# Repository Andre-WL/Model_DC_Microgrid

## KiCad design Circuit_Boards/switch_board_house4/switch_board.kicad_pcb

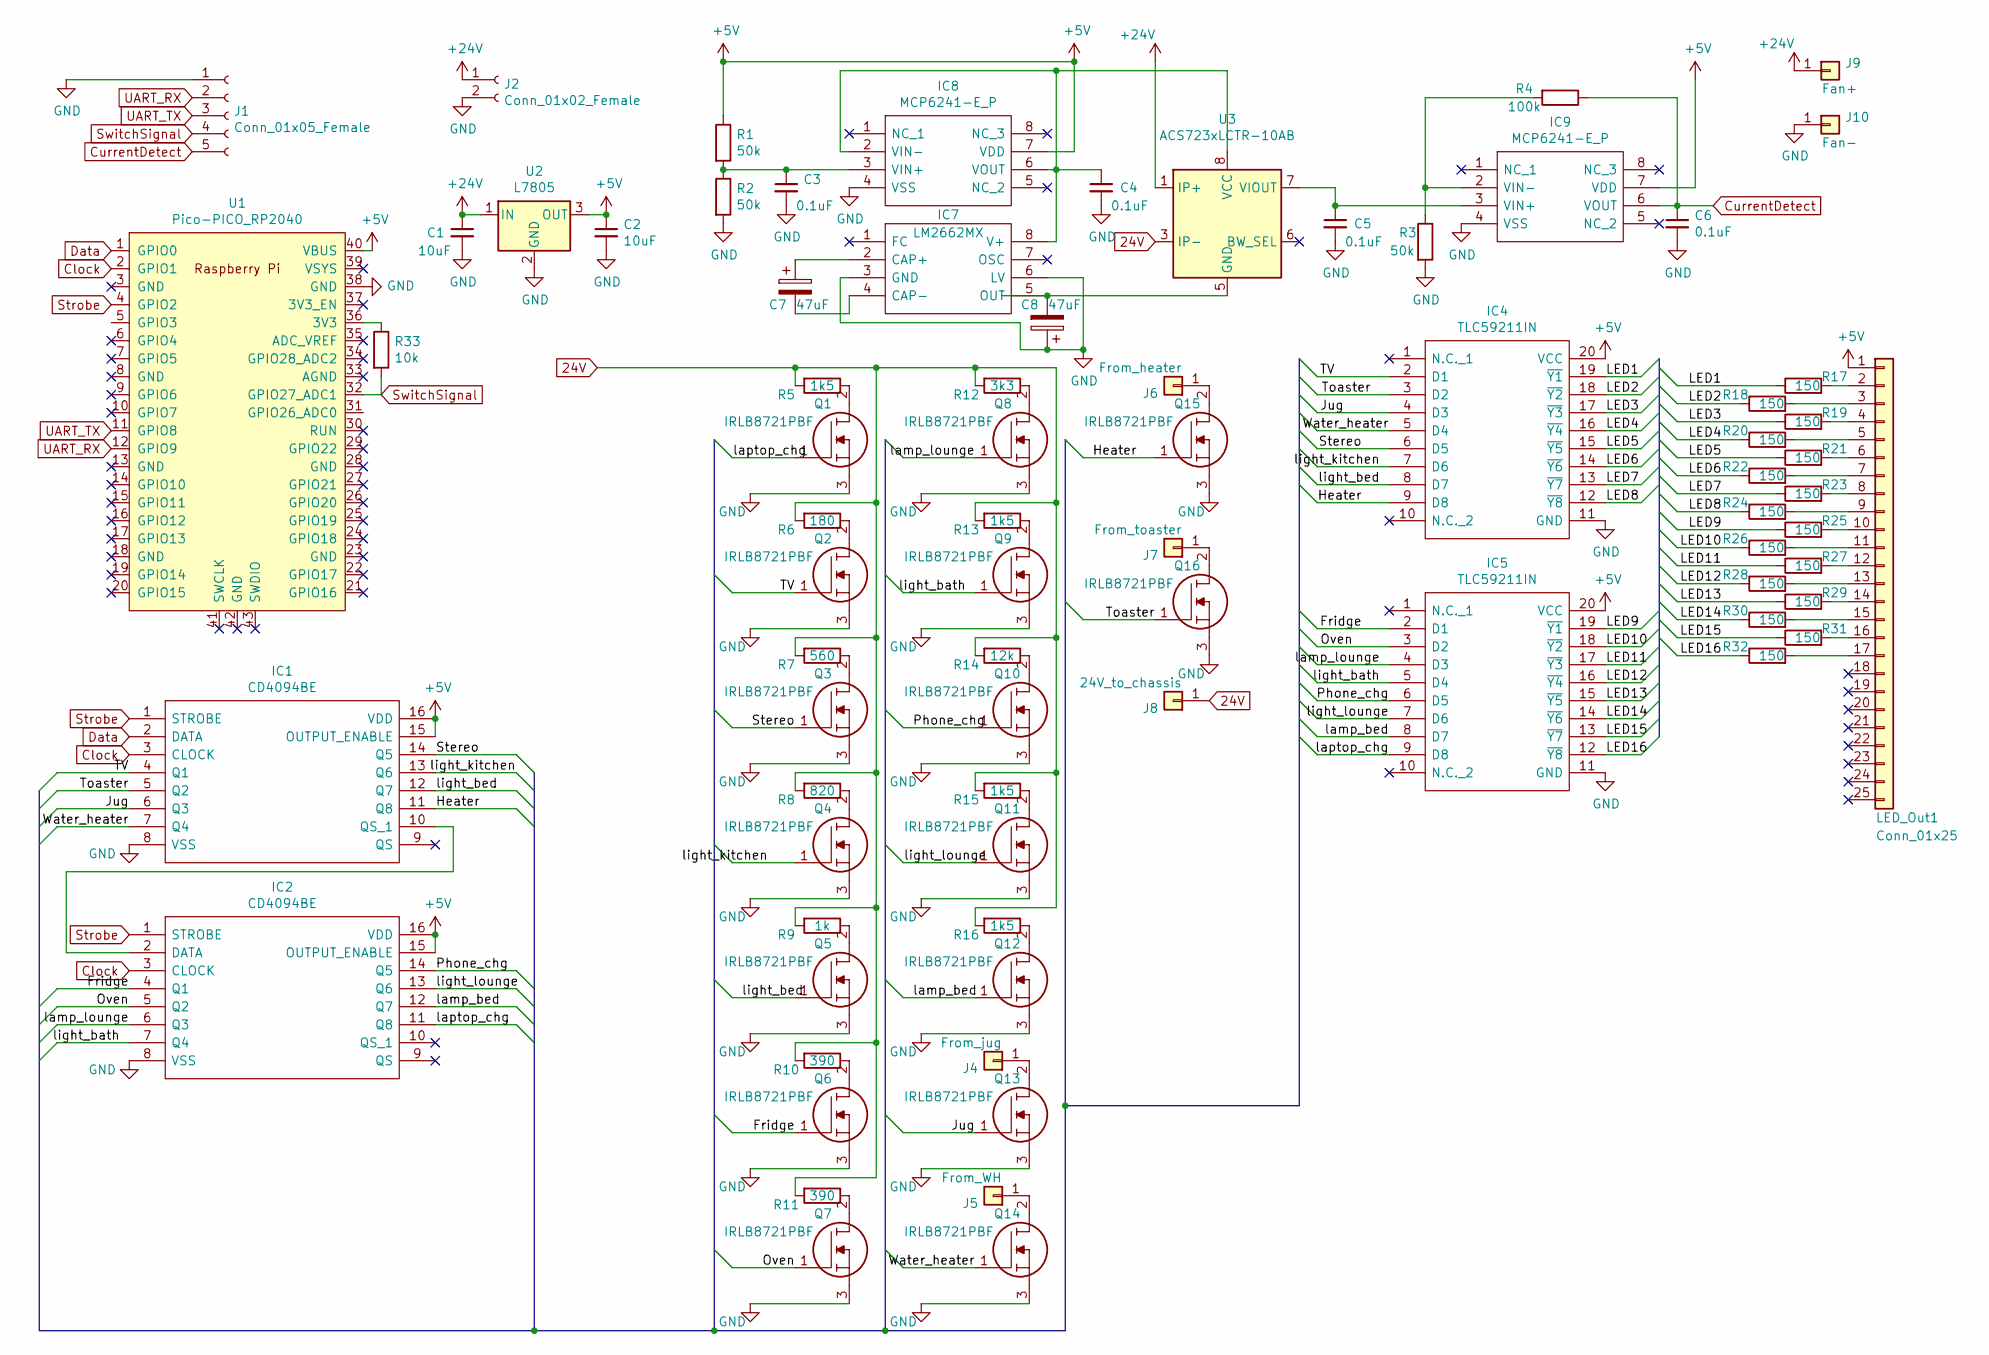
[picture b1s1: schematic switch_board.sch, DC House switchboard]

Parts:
C1, C2: 10uF; C_Disc_D5.0mm_W2.5mm_P2.50mm
C3, C4, C5, C6: 0.1uF; C320C104J3G5TA
C7, C8: 47uF; CAPAE825X1030N
IC1, IC2: CD4094BE; DIP794W53P254L1930H508Q16N; Manufacturer_Part_Number CD4094BE; Mouser Part Number 595-CD4094BE
IC4, IC5: TLC59211IN; DIP794W53P254L2540H508Q20N; Manufacturer_Part_Number TLC59211IN; Mouser Part Number 595-TLC59211IN
IC7: LM2662MX; SOIC127P600X175-8N; Manufacturer_Part_Number LM2662MX; Mouser Part Number 926-LM2662MX
IC8, IC9: MCP6241-E_P; DIP781W56P254L950H533Q8N; Manufacturer_Part_Number MCP6241-E/P; Mouser Part Number 579-MCP6241-E/P
J1: Conn_01x05_Female; SolderWire-2.5sqmm_1x05_P8.8mm_D2.4mm_OD4.4mm
J2: Conn_01x02_Female; SolderWire-2.5sqmm_1x02_P8.8mm_D2.4mm_OD4.4mm
J4: From_jug; SolderWire-2.5sqmm_1x01_D2.4mm_OD3.6mm
J5: From_WH; SolderWire-2.5sqmm_1x01_D2.4mm_OD3.6mm
J6: From_heater; SolderWire-2.5sqmm_1x01_D2.4mm_OD3.6mm
J7: From_toaster; SolderWire-2.5sqmm_1x01_D2.4mm_OD3.6mm
J8: 24V_to_chassis; SolderWire-2.5sqmm_1x01_D2.4mm_OD3.6mm
J9: Fan+; SolderWire-2.5sqmm_1x01_D2.4mm_OD3.6mm
J10: Fan-; SolderWire-2.5sqmm_1x01_D2.4mm_OD3.6mm
LED_Out1: Conn_01x25; PinHeader_1x25_P2.54mm_Vertical
Q1, Q2, Q3, Q4, Q5, Q6, Q7, Q8, Q9, Q10, Q11, Q12, Q13, Q14, Q15, Q16: IRLB8721PBF; TO254P483X1016X1994-3P; Manufacturer_Part_Number IRLB8721PBF; Mouser Part Number 942-IRLB8721PBF
R1, R2, R3: 50k; R_Axial_DIN0207_L6.3mm_D2.5mm_P10.16mm_Horizontal
R4: 100k; R_Axial_DIN0207_L6.3mm_D2.5mm_P10.16mm_Horizontal
R5, R13, R15, R16: 1k5; LR1F1K5
R6: 180; ROX5SS
R7: 560; ROX2SJ560R
R8: 820; MFP1_res
R9: 1k; 1K_load
R10, R11: 390; ROX5SS
R12: 3k3; LR1F3K3
R14: 12k; LR1F1K5
R17, R18, R19, R20, R21, R22, R23, R24, R25, R26, R27, R28, R29, R30, R31, R32: 150; RNMF14FTC150R
R33: 10k; R_Axial_DIN0207_L6.3mm_D2.5mm_P10.16mm_Horizontal
U1: Pico-PICO_RP2040; PinHeader_2x20_P2.54mm_PICO
U2: L7805; TO255P460X1020X2008-3P
U3: ACS723xLCTR-10AB; SOIC-8_3.9x4.9mm_P1.27mm

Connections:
24V: J8.1, R5.2, R6.2, R7.2, R8.2, R9.2, R10.2, R11.2, R12.2, R13.2, R14.2, R15.2, R16.2, U3.3 (IP-), U3.4 (IP-)
+5V: C2.1, IC1.15 (OUTPUT_ENABLE), IC1.16 (VDD), IC2.15 (OUTPUT_ENABLE), IC2.16 (VDD), IC4.20 (VCC), IC5.20 (VCC), IC8.7 (VDD), IC9.7 (VDD), LED_Out1.1, R1.1, U1.40 (VBUS), U2.3 (OUT)
+24V: C1.1, J2.1, J9.1, U2.1 (IN), U3.1 (IP+), U3.2 (IP+)
/Fridge: IC2.4 (Q1), IC5.2 (D1), Q6.1
/Heater: IC1.11 (Q8), IC4.9 (D8), Q15.1
/Jug: IC1.6 (Q3), IC4.4 (D3), Q13.1
/LED1: IC4.19 (~Y1), R17.1
/LED2: IC4.18 (~Y2), R18.1
/LED3: IC4.17 (~Y3), R19.1
/LED4: IC4.16 (~Y4), R20.1
/LED5: IC4.15 (~Y5), R21.1
/LED6: IC4.14 (~Y6), R22.1
/LED7: IC4.13 (~Y7), R23.1
/LED8: IC4.12 (~Y8), R24.1
/LED9: IC5.19 (~Y1), R25.1
/LED10: IC5.18 (~Y2), R26.1
/LED11: IC5.17 (~Y3), R27.1
/LED12: IC5.16 (~Y4), R28.1
/LED13: IC5.15 (~Y5), R29.1
/LED14: IC5.14 (~Y6), R30.1
/LED15: IC5.13 (~Y7), R31.1
/LED16: IC5.12 (~Y8), R32.1
/Oven: IC2.5 (Q2), IC5.3 (D2), Q7.1
/Phone_chg: IC2.14 (Q5), IC5.6 (D5), Q10.1
/Stereo: IC1.14 (Q5), IC4.6 (D5), Q3.1
/TV: IC1.4 (Q1), IC4.2 (D1), Q2.1
/Toaster: IC1.5 (Q2), IC4.3 (D2), Q16.1
/Water_heater: IC1.7 (Q4), IC4.5 (D4), Q14.1
/lamp_bed: IC2.12 (Q7), IC5.8 (D7), Q12.1
/lamp_lounge: IC2.6 (Q3), IC5.4 (D3), Q8.1
/laptop_chg: IC2.11 (Q8), IC5.9 (D8), Q1.1
/light_bath: IC2.7 (Q4), IC5.5 (D4), Q9.1
/light_bed: IC1.12 (Q7), IC4.8 (D7), Q5.1
/light_kitchen: IC1.13 (Q6), IC4.7 (D6), Q4.1
/light_lounge: IC2.13 (Q6), IC5.7 (D6), Q11.1
Clock: IC1.3 (CLOCK), IC2.3 (CLOCK), U1.2 (GPIO1)
CurrentDetect: C6.1, IC9.6 (VOUT), J1.5, R4.1
Data: IC1.2 (DATA), U1.1 (GPIO0)
GND: C1.2, C2.2, C3.2, C4.2, C5.2, C6.2, C8.1, IC1.8 (VSS), IC2.8 (VSS), IC4.11 (GND), IC5.11 (GND), IC7.3 (GND), IC7.6 (LV), IC8.4 (VSS), IC9.4 (VSS), J1.1, J2.2, J10.1, Q1.3, Q2.3, Q3.3, Q4.3, Q5.3, Q6.3, Q7.3, Q8.3, Q9.3, Q10.3, Q11.3, Q12.3, Q13.3, Q14.3, Q15.3, Q16.3, R2.2, R3.2, U1.38 (GND), U2.2 (GND)
unnamed: C3.1, IC8.3 (VIN+), R1.2, R2.1
unnamed: C4.1, IC7.8 (V+), IC8.2 (VIN-), IC8.6 (VOUT), U3.8 (VCC)
unnamed: C5.1, IC9.3 (VIN+), U3.7 (VIOUT)
unnamed: C7.1, IC7.2 (CAP+)
unnamed: C7.2, IC7.4 (CAP-)
unnamed: C8.2, IC7.5 (OUT), U3.5 (GND)
unnamed: IC1.10 (QS_1), IC2.2 (DATA)
unnamed: IC9.2 (VIN-), R3.1, R4.2
unnamed: J4.1, Q13.2
unnamed: J5.1, Q14.2
unnamed: J6.1, Q15.2
unnamed: J7.1, Q16.2
unnamed: LED_Out1.2, R17.2
unnamed: LED_Out1.3, R18.2
unnamed: LED_Out1.4, R19.2
unnamed: LED_Out1.5, R20.2
unnamed: LED_Out1.6, R21.2
unnamed: LED_Out1.7, R22.2
unnamed: LED_Out1.8, R23.2
unnamed: LED_Out1.9, R24.2
unnamed: LED_Out1.10, R25.2
unnamed: LED_Out1.11, R26.2
unnamed: LED_Out1.12, R27.2
unnamed: LED_Out1.13, R28.2
unnamed: LED_Out1.14, R29.2
unnamed: LED_Out1.15, R30.2
unnamed: LED_Out1.16, R31.2
unnamed: LED_Out1.17, R32.2
unnamed: Q1.2, R5.1
unnamed: Q2.2, R6.1
unnamed: Q3.2, R7.1
unnamed: Q4.2, R8.1
unnamed: Q5.2, R9.1
unnamed: Q6.2, R10.1
unnamed: Q7.2, R11.1
unnamed: Q8.2, R12.1
unnamed: Q9.2, R13.1
unnamed: Q10.2, R14.1
unnamed: Q11.2, R15.1
unnamed: Q12.2, R16.1
unnamed: R33.1, U1.36 (3V3)
Strobe: IC1.1 (STROBE), IC2.1 (STROBE), U1.4 (GPIO2)
SwitchSignal: J1.4, R33.2, U1.32 (GPIO27_ADC1)
UART_RX: J1.2, U1.12 (GPIO9)
UART_TX: J1.3, U1.11 (GPIO8)

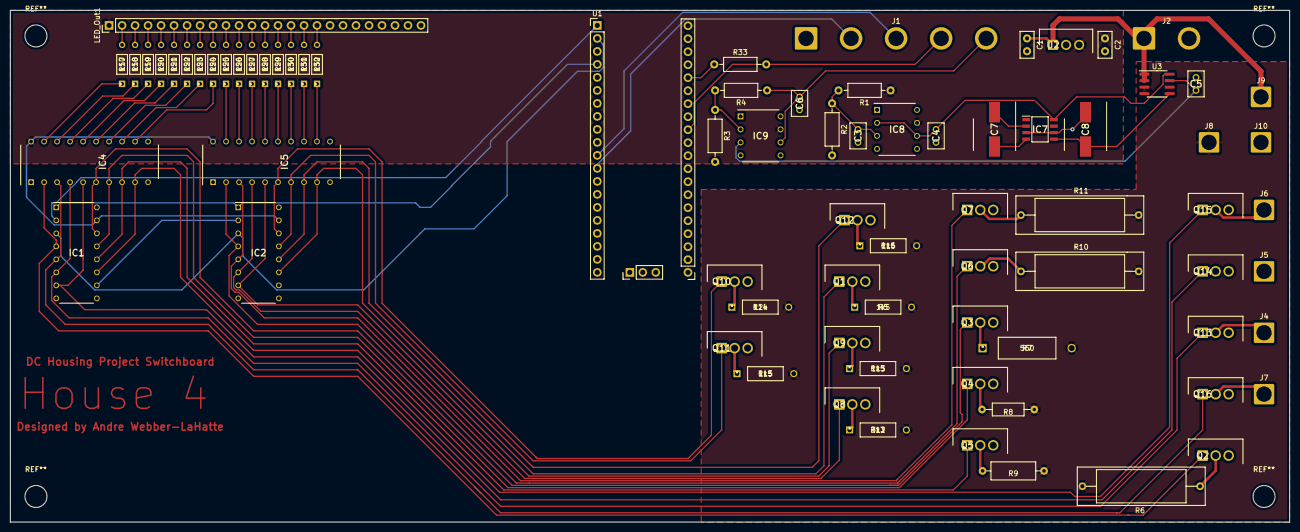
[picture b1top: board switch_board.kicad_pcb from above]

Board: 2 copper layers, 250.0 x 100.0 mm, 77 parts (0 on the bottom side), 84 nets.

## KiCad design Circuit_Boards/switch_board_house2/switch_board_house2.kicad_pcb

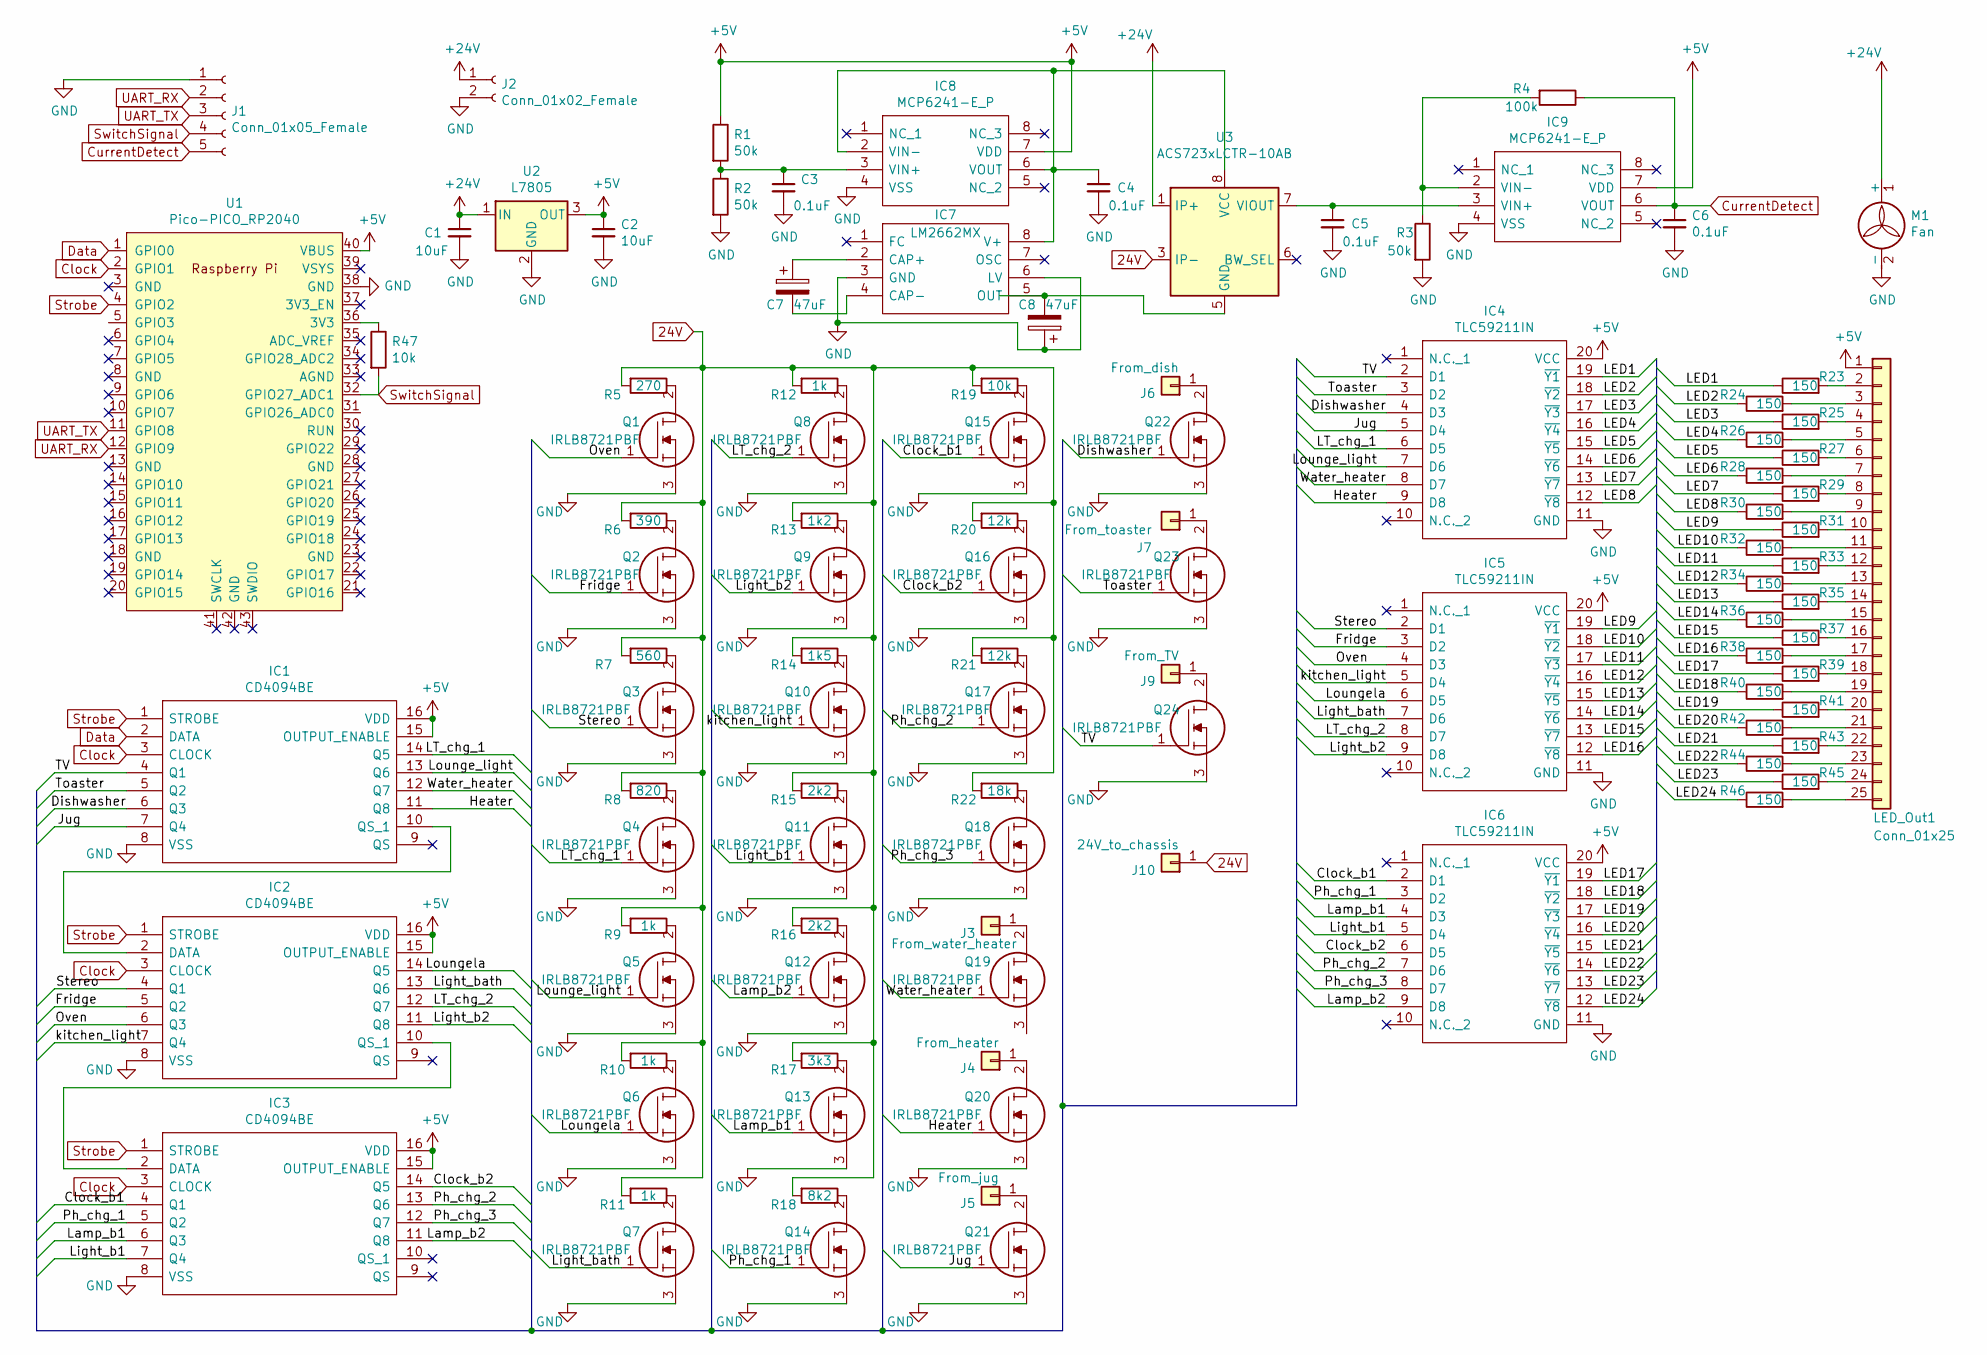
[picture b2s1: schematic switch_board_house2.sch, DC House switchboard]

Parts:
C1, C2: 10uF; C_Disc_D5.0mm_W2.5mm_P2.50mm
C3, C4, C5, C6: 0.1uF; C320C104J3G5TA
C7, C8: 47uF; CAPAE825X1030N
IC1, IC2, IC3: CD4094BE; DIP794W53P254L1930H508Q16N; Manufacturer_Part_Number CD4094BE; Mouser Part Number 595-CD4094BE
IC4, IC5, IC6: TLC59211IN; DIP794W53P254L2540H508Q20N; Manufacturer_Part_Number TLC59211IN; Mouser Part Number 595-TLC59211IN
IC7: LM2662MX; SOIC127P600X175-8N; Manufacturer_Part_Number LM2662MX; Mouser Part Number 926-LM2662MX
IC8, IC9: MCP6241-E_P; DIP781W56P254L950H533Q8N; Manufacturer_Part_Number MCP6241-E/P; Mouser Part Number 579-MCP6241-E/P
J1: Conn_01x05_Female; SolderWire-2.5sqmm_1x05_P8.8mm_D2.4mm_OD4.4mm
J2: Conn_01x02_Female; SolderWire-2.5sqmm_1x02_P8.8mm_D2.4mm_OD4.4mm
J3: From_water_heater; SolderWire-2.5sqmm_1x01_D2.4mm_OD3.6mm
J4: From_heater; SolderWire-2.5sqmm_1x01_D2.4mm_OD3.6mm
J5: From_jug; SolderWire-2.5sqmm_1x01_D2.4mm_OD3.6mm
J6: From_dish; SolderWire-2.5sqmm_1x01_D2.4mm_OD3.6mm
J7: From_toaster; SolderWire-2.5sqmm_1x01_D2.4mm_OD3.6mm
J9: From_TV; SolderWire-2.5sqmm_1x01_D2.4mm_OD3.6mm
J10: 24V_to_chassis; SolderWire-2.5sqmm_1x01_D2.4mm_OD3.6mm
LED_Out1: Conn_01x25; PinHeader_1x25_P2.54mm_Vertical
M1: Fan; SolderWire-2.5sqmm_1x02_P8.8mm_D2.4mm_OD4.4mm
Q1, Q2, Q3, Q4, Q5, Q6, Q7, Q8, Q9, Q10, Q11, Q12, Q13, Q14, Q15, Q16, Q17, Q18, Q19, Q20, Q21, Q22, Q23, Q24: IRLB8721PBF; TO254P483X1016X1994-3P; Manufacturer_Part_Number IRLB8721PBF; Mouser Part Number 942-IRLB8721PBF
R1, R2, R3: 50k; R_Axial_DIN0207_L6.3mm_D2.5mm_P10.16mm_Horizontal
R4: 100k; R_Axial_DIN0207_L6.3mm_D2.5mm_P10.16mm_Horizontal
R5: 270; ROX5SS
R6: 390; ROX5SS
R7: 560; ROX2SJ560R
R8: 820; MFP1_res
R9, R10, R11, R12: 1k; 1K_load
R13: 1k2; 1k2_res_v2
R14: 1k5; LR1F1K5
R15, R16: 2k2; LR1F1K5
R17: 3k3; LR1F3K3
R18: 8k2; LR1F1K5
R19: 10k; 10k_res
R20, R21: 12k; LR1F1K5
R22: 18k; 18k_res
R23, R24, R25, R26, R27, R28, R29, R30, R31, R32, R33, R34, R35, R36, R37, R38, R39, R40, R41, R42, R43, R44, R45, R46: 150; RNMF14FTC150R
R47: 10k; R_Axial_DIN0207_L6.3mm_D2.5mm_P10.16mm_Horizontal
U1: Pico-PICO_RP2040; PinHeader_2x20_P2.54mm_PICO
U2: L7805; TO255P460X1020X2008-3P
U3: ACS723xLCTR-10AB; SOIC-8_3.9x4.9mm_P1.27mm

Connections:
24V: J10.1, R5.2, R6.2, R7.2, R8.2, R9.2, R10.2, R11.2, R12.2, R13.2, R14.2, R15.2, R16.2, R17.2, R18.2, R19.2, R20.2, R21.2, R22.2, U3.3 (IP-), U3.4 (IP-)
+5V: C2.1, IC1.15 (OUTPUT_ENABLE), IC1.16 (VDD), IC2.15 (OUTPUT_ENABLE), IC2.16 (VDD), IC3.15 (OUTPUT_ENABLE), IC3.16 (VDD), IC4.20 (VCC), IC5.20 (VCC), IC6.20 (VCC), IC8.7 (VDD), IC9.7 (VDD), LED_Out1.1, R1.1, U1.40 (VBUS), U2.3 (OUT)
+24V: C1.1, J2.1, M1.1 (+), U2.1 (IN), U3.1 (IP+), U3.2 (IP+)
/Clock_b1: IC3.4 (Q1), IC6.2 (D1), Q15.1
/Clock_b2: IC3.14 (Q5), IC6.6 (D5), Q16.1
/Dishwasher: IC1.6 (Q3), IC4.4 (D3), Q22.1
/Fridge: IC2.5 (Q2), IC5.3 (D2), Q2.1
/Heater: IC1.11 (Q8), IC4.9 (D8), Q20.1
/Jug: IC1.7 (Q4), IC4.5 (D4), Q21.1
/LED1: IC4.19 (~Y1), R23.1
/LED2: IC4.18 (~Y2), R24.1
/LED3: IC4.17 (~Y3), R25.1
/LED4: IC4.16 (~Y4), R26.1
/LED5: IC4.15 (~Y5), R27.1
/LED6: IC4.14 (~Y6), R28.1
/LED7: IC4.13 (~Y7), R29.1
/LED8: IC4.12 (~Y8), R30.1
/LED9: IC5.19 (~Y1), R31.1
/LED10: IC5.18 (~Y2), R32.1
/LED11: IC5.17 (~Y3), R33.1
/LED12: IC5.16 (~Y4), R34.1
/LED13: IC5.15 (~Y5), R35.1
/LED14: IC5.14 (~Y6), R36.1
/LED15: IC5.13 (~Y7), R37.1
/LED16: IC5.12 (~Y8), R38.1
/LED17: IC6.19 (~Y1), R39.1
/LED18: IC6.18 (~Y2), R40.1
/LED19: IC6.17 (~Y3), R41.1
/LED20: IC6.16 (~Y4), R42.1
/LED21: IC6.15 (~Y5), R43.1
/LED22: IC6.14 (~Y6), R44.1
/LED23: IC6.13 (~Y7), R45.1
/LED24: IC6.12 (~Y8), R46.1
/LT_chg_1: IC1.14 (Q5), IC4.6 (D5), Q4.1
/LT_chg_2: IC2.12 (Q7), IC5.8 (D7), Q8.1
/Lamp_b1: IC3.6 (Q3), IC6.4 (D3), Q13.1
/Lamp_b2: IC3.11 (Q8), IC6.9 (D8), Q12.1
/Light_b1: IC3.7 (Q4), IC6.5 (D4), Q11.1
/Light_b2: IC2.11 (Q8), IC5.9 (D8), Q9.1
/Light_bath: IC2.13 (Q6), IC5.7 (D6), Q7.1
/Lounge_light: IC1.13 (Q6), IC4.7 (D6), Q5.1
/Loungela: IC2.14 (Q5), IC5.6 (D5), Q6.1
/Oven: IC2.6 (Q3), IC5.4 (D3), Q1.1
/Ph_chg_1: IC3.5 (Q2), IC6.3 (D2), Q14.1
/Ph_chg_2: IC3.13 (Q6), IC6.7 (D6), Q17.1
/Ph_chg_3: IC3.12 (Q7), IC6.8 (D7), Q18.1
/Stereo: IC2.4 (Q1), IC5.2 (D1), Q3.1
/TV: IC1.4 (Q1), IC4.2 (D1), Q24.1
/Toaster: IC1.5 (Q2), IC4.3 (D2), Q23.1
/Water_heater: IC1.12 (Q7), IC4.8 (D7), Q19.1
/kitchen_light: IC2.7 (Q4), IC5.5 (D4), Q10.1
Clock: IC1.3 (CLOCK), IC2.3 (CLOCK), IC3.3 (CLOCK), U1.2 (GPIO1)
CurrentDetect: C6.1, IC9.6 (VOUT), J1.5, R4.1
Data: IC1.2 (DATA), U1.1 (GPIO0)
GND: C1.2, C2.2, C3.2, C4.2, C5.2, C6.2, C8.1, IC1.8 (VSS), IC2.8 (VSS), IC3.8 (VSS), IC4.11 (GND), IC5.11 (GND), IC6.11 (GND), IC7.3 (GND), IC7.6 (LV), IC8.4 (VSS), IC9.4 (VSS), J1.1, J2.2, M1.2 (-), Q1.3, Q2.3, Q3.3, Q4.3, Q5.3, Q6.3, Q7.3, Q8.3, Q9.3, Q10.3, Q11.3, Q12.3, Q13.3, Q14.3, Q15.3, Q16.3, Q17.3, Q18.3, Q20.3, Q21.3, Q22.3, Q23.3, Q24.3, R2.2, R3.2, U1.38 (GND), U2.2 (GND)
unnamed: C3.1, IC8.3 (VIN+), R1.2, R2.1
unnamed: C4.1, IC7.8 (V+), IC8.2 (VIN-), IC8.6 (VOUT), U3.8 (VCC)
unnamed: C5.1, IC9.3 (VIN+), U3.7 (VIOUT)
unnamed: C7.1, IC7.2 (CAP+)
unnamed: C7.2, IC7.4 (CAP-)
unnamed: C8.2, IC7.5 (OUT), U3.5 (GND)
unnamed: IC1.10 (QS_1), IC2.2 (DATA)
unnamed: IC2.10 (QS_1), IC3.2 (DATA)
unnamed: IC9.2 (VIN-), R3.1, R4.2
unnamed: J3.1, Q19.2
unnamed: J4.1, Q20.2
unnamed: J5.1, Q21.2
unnamed: J6.1, Q22.2
unnamed: J7.1, Q23.2
unnamed: J9.1, Q24.2
unnamed: LED_Out1.2, R23.2
unnamed: LED_Out1.3, R24.2
unnamed: LED_Out1.4, R25.2
unnamed: LED_Out1.5, R26.2
unnamed: LED_Out1.6, R27.2
unnamed: LED_Out1.7, R28.2
unnamed: LED_Out1.8, R29.2
unnamed: LED_Out1.9, R30.2
unnamed: LED_Out1.10, R31.2
unnamed: LED_Out1.11, R32.2
unnamed: LED_Out1.12, R33.2
unnamed: LED_Out1.13, R34.2
unnamed: LED_Out1.14, R35.2
unnamed: LED_Out1.15, R36.2
unnamed: LED_Out1.16, R37.2
unnamed: LED_Out1.17, R38.2
unnamed: LED_Out1.18, R39.2
unnamed: LED_Out1.19, R40.2
unnamed: LED_Out1.20, R41.2
unnamed: LED_Out1.21, R42.2
unnamed: LED_Out1.22, R43.2
unnamed: LED_Out1.23, R44.2
unnamed: LED_Out1.24, R45.2
unnamed: LED_Out1.25, R46.2
unnamed: Q1.2, R5.1
unnamed: Q2.2, R6.1
unnamed: Q3.2, R7.1
unnamed: Q4.2, R8.1
unnamed: Q5.2, R9.1
unnamed: Q6.2, R10.1
unnamed: Q7.2, R11.1
unnamed: Q8.2, R12.1
unnamed: Q9.2, R13.1
unnamed: Q10.2, R14.1
unnamed: Q11.2, R15.1
unnamed: Q12.2, R16.1
unnamed: Q13.2, R17.1
unnamed: Q14.2, R18.1
unnamed: Q15.2, R19.1
unnamed: Q16.2, R20.1
unnamed: Q17.2, R21.1
unnamed: Q18.2, R22.1
unnamed: R47.1, U1.36 (3V3)
Strobe: IC1.1 (STROBE), IC2.1 (STROBE), IC3.1 (STROBE), U1.4 (GPIO2)
SwitchSignal: J1.4, R47.2, U1.32 (GPIO27_ADC1)
UART_RX: J1.2, U1.12 (GPIO9)
UART_TX: J1.3, U1.11 (GPIO8)

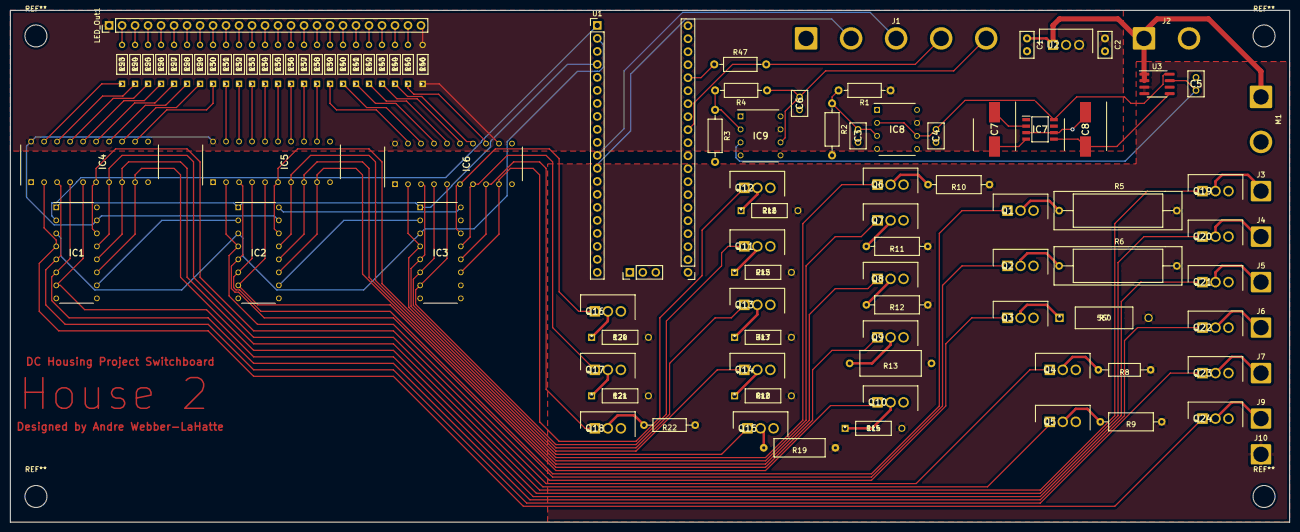
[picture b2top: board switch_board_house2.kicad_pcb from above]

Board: 2 copper layers, 250.0 x 100.0 mm, 102 parts (0 on the bottom side), 117 nets.

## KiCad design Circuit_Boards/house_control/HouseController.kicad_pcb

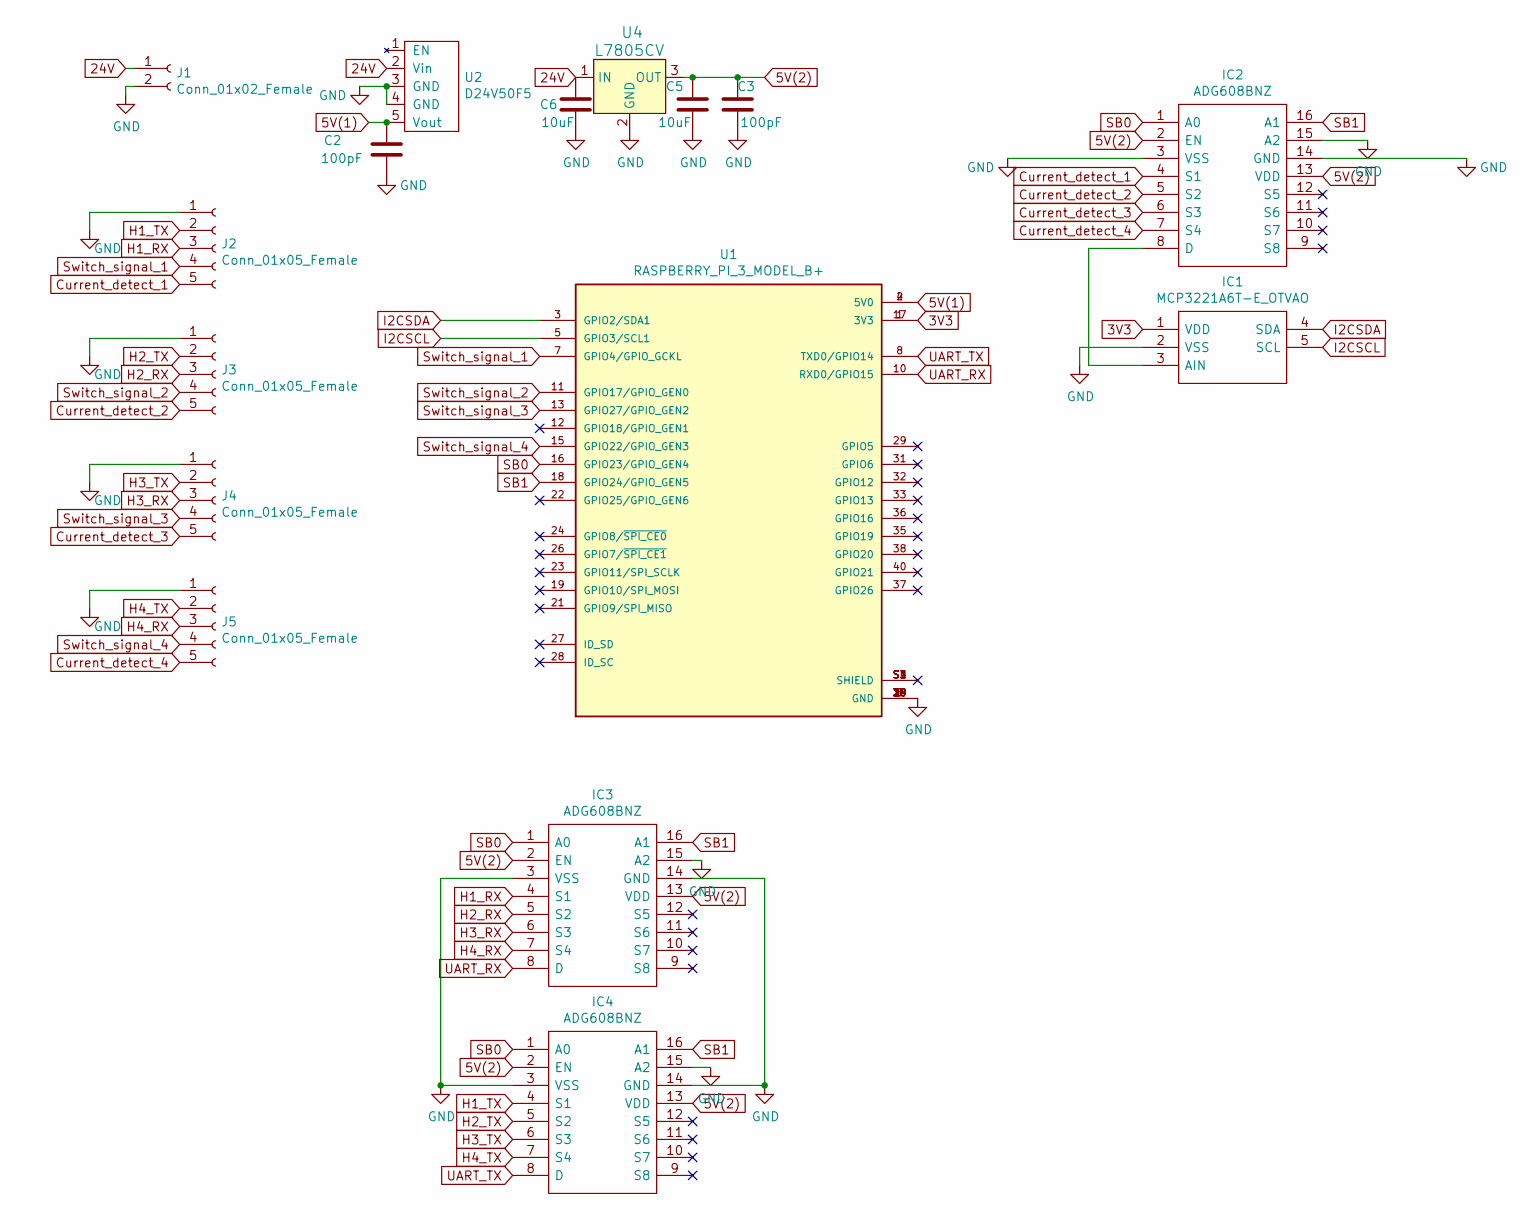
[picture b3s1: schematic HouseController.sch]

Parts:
C2, C3: 100pF; C320C104J3G5TA
C5, C6: 10uF; C_Disc_D5.0mm_W2.5mm_P2.50mm
IC1: MCP3221A6T-E_OTVAO; SOT95P280X145-5N; Manufacturer_Part_Number MCP3221A6T-E/OTVAO; Mouser Part Number 579-MCP3221A6TEOTVAO
IC2, IC3, IC4: ADG608BNZ; DIP794W56P254L2013H533Q16N; Manufacturer_Part_Number ADG608BNZ; Mouser Part Number 584-ADG608BNZ
J1: Conn_01x02_Female; SolderWire-2.5sqmm_1x02_P8.8mm_D2.4mm_OD4.4mm
J2, J3, J4, J5: Conn_01x05_Female; SolderWire-0.5sqmm_1x05_P4.6mm_D0.9mm_OD2.1mm
U1: RASPBERRY_PI_3_MODEL_B+; MODULE_RASPBERRY_PI_3_MODEL_B+; PARTREV 1.0
U2: D24V50F5; PinHeader_1x05_P2.54mm_Vertical
U4: L7805CV; TO255P460X1020X2008-3P; MPN L7805CV; Digi-Key_PN 497-1443-5-ND

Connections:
3V3: IC1.1 (VDD), U1.1 (3V3), U1.17 (3V3)
5V(1): C2.1, U1.2 (5V0), U1.4 (5V0), U2.5 (Vout)
5V(2): C3.2, C5.1, IC2.2 (EN), IC2.13 (VDD), IC3.2 (EN), IC3.13 (VDD), IC4.2 (EN), IC4.13 (VDD), U4.3 (OUT)
24V: C6.1, J1.1, U2.2 (Vin), U4.1 (IN)
Current_detect_1: IC2.4 (S1), J2.5
Current_detect_2: IC2.5 (S2), J3.5
Current_detect_3: IC2.6 (S3), J4.5
Current_detect_4: IC2.7 (S4), J5.5
GND: C2.2, C3.1, C5.2, C6.2, IC1.2 (VSS), IC2.3 (VSS), IC2.14 (GND), IC2.15 (A2), IC3.3 (VSS), IC3.14 (GND), IC3.15 (A2), IC4.3 (VSS), IC4.14 (GND), IC4.15 (A2), J1.2, J2.1, J3.1, J4.1, J5.1, U1.6 (GND), U1.9 (GND), U1.14 (GND), U1.20 (GND), U1.25 (GND), U1.30 (GND), U1.34 (GND), U1.39 (GND), U2.3 (GND), U2.4 (GND), U4.2 (GND)
H1_RX: IC3.4 (S1), J2.3
H1_TX: IC4.4 (S1), J2.2
H2_RX: IC3.5 (S2), J3.3
H2_TX: IC4.5 (S2), J3.2
H3_RX: IC3.6 (S3), J4.3
H3_TX: IC4.6 (S3), J4.2
H4_RX: IC3.7 (S4), J5.3
H4_TX: IC4.7 (S4), J5.2
I2CSCL: IC1.5 (SCL), U1.5 (GPIO3/SCL1)
I2CSDA: IC1.4 (SDA), U1.3 (GPIO2/SDA1)
unnamed: IC1.3 (AIN), IC2.8 (D)
unnamed: U1.S1 (SHIELD), U1.S2 (SHIELD), U1.S3 (SHIELD), U1.S4 (SHIELD)
SB0: IC2.1 (A0), IC3.1 (A0), IC4.1 (A0), U1.16 (GPIO23/GPIO_GEN4)
SB1: IC2.16 (A1), IC3.16 (A1), IC4.16 (A1), U1.18 (GPIO24/GPIO_GEN5)
Switch_signal_1: J2.4, U1.7 (GPIO4/GPIO_GCKL)
Switch_signal_2: J3.4, U1.11 (GPIO17/GPIO_GEN0)
Switch_signal_3: J4.4, U1.13 (GPIO27/GPIO_GEN2)
Switch_signal_4: J5.4, U1.15 (GPIO22/GPIO_GEN3)
UART_RX: IC3.8 (D), U1.10 (RXD0/GPIO15)
UART_TX: IC4.8 (D), U1.8 (TXD0/GPIO14)

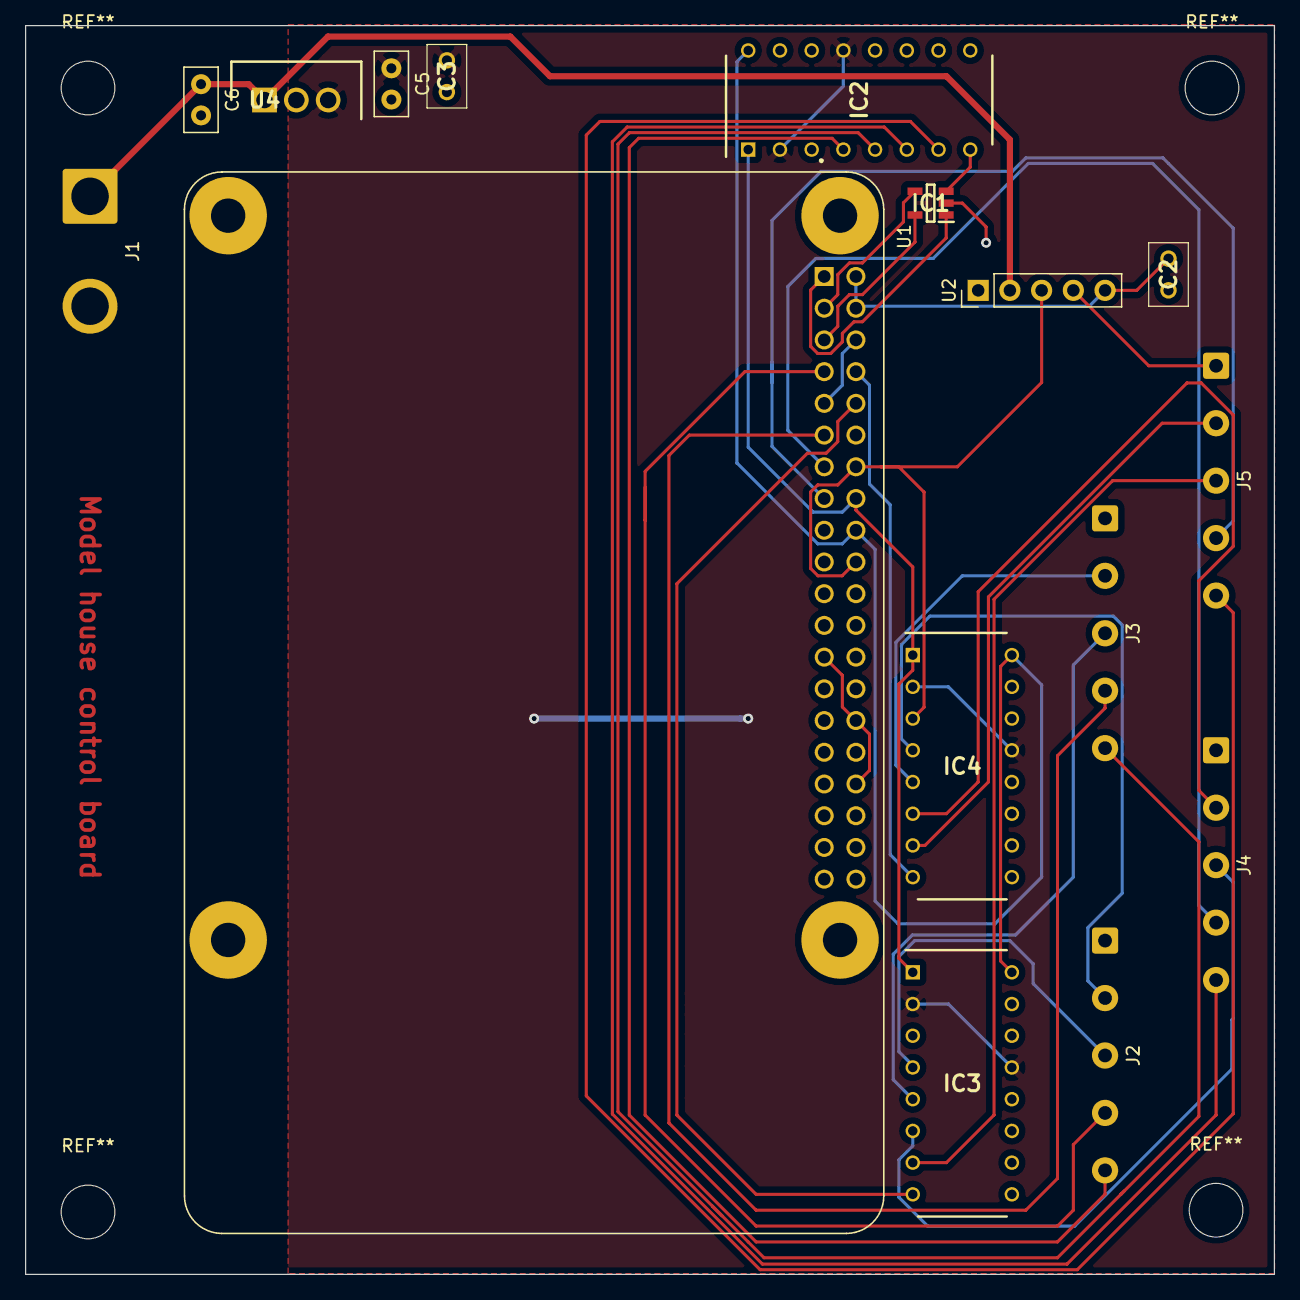
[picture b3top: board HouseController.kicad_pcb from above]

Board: 2 copper layers, 100.0 x 100.0 mm, 16 parts (0 on the bottom side), 29 nets.

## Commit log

2022-10-04 Adding all files

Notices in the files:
parts and their libraries:
Copyright 2021 Accelerated Designs. All rights reserved.
